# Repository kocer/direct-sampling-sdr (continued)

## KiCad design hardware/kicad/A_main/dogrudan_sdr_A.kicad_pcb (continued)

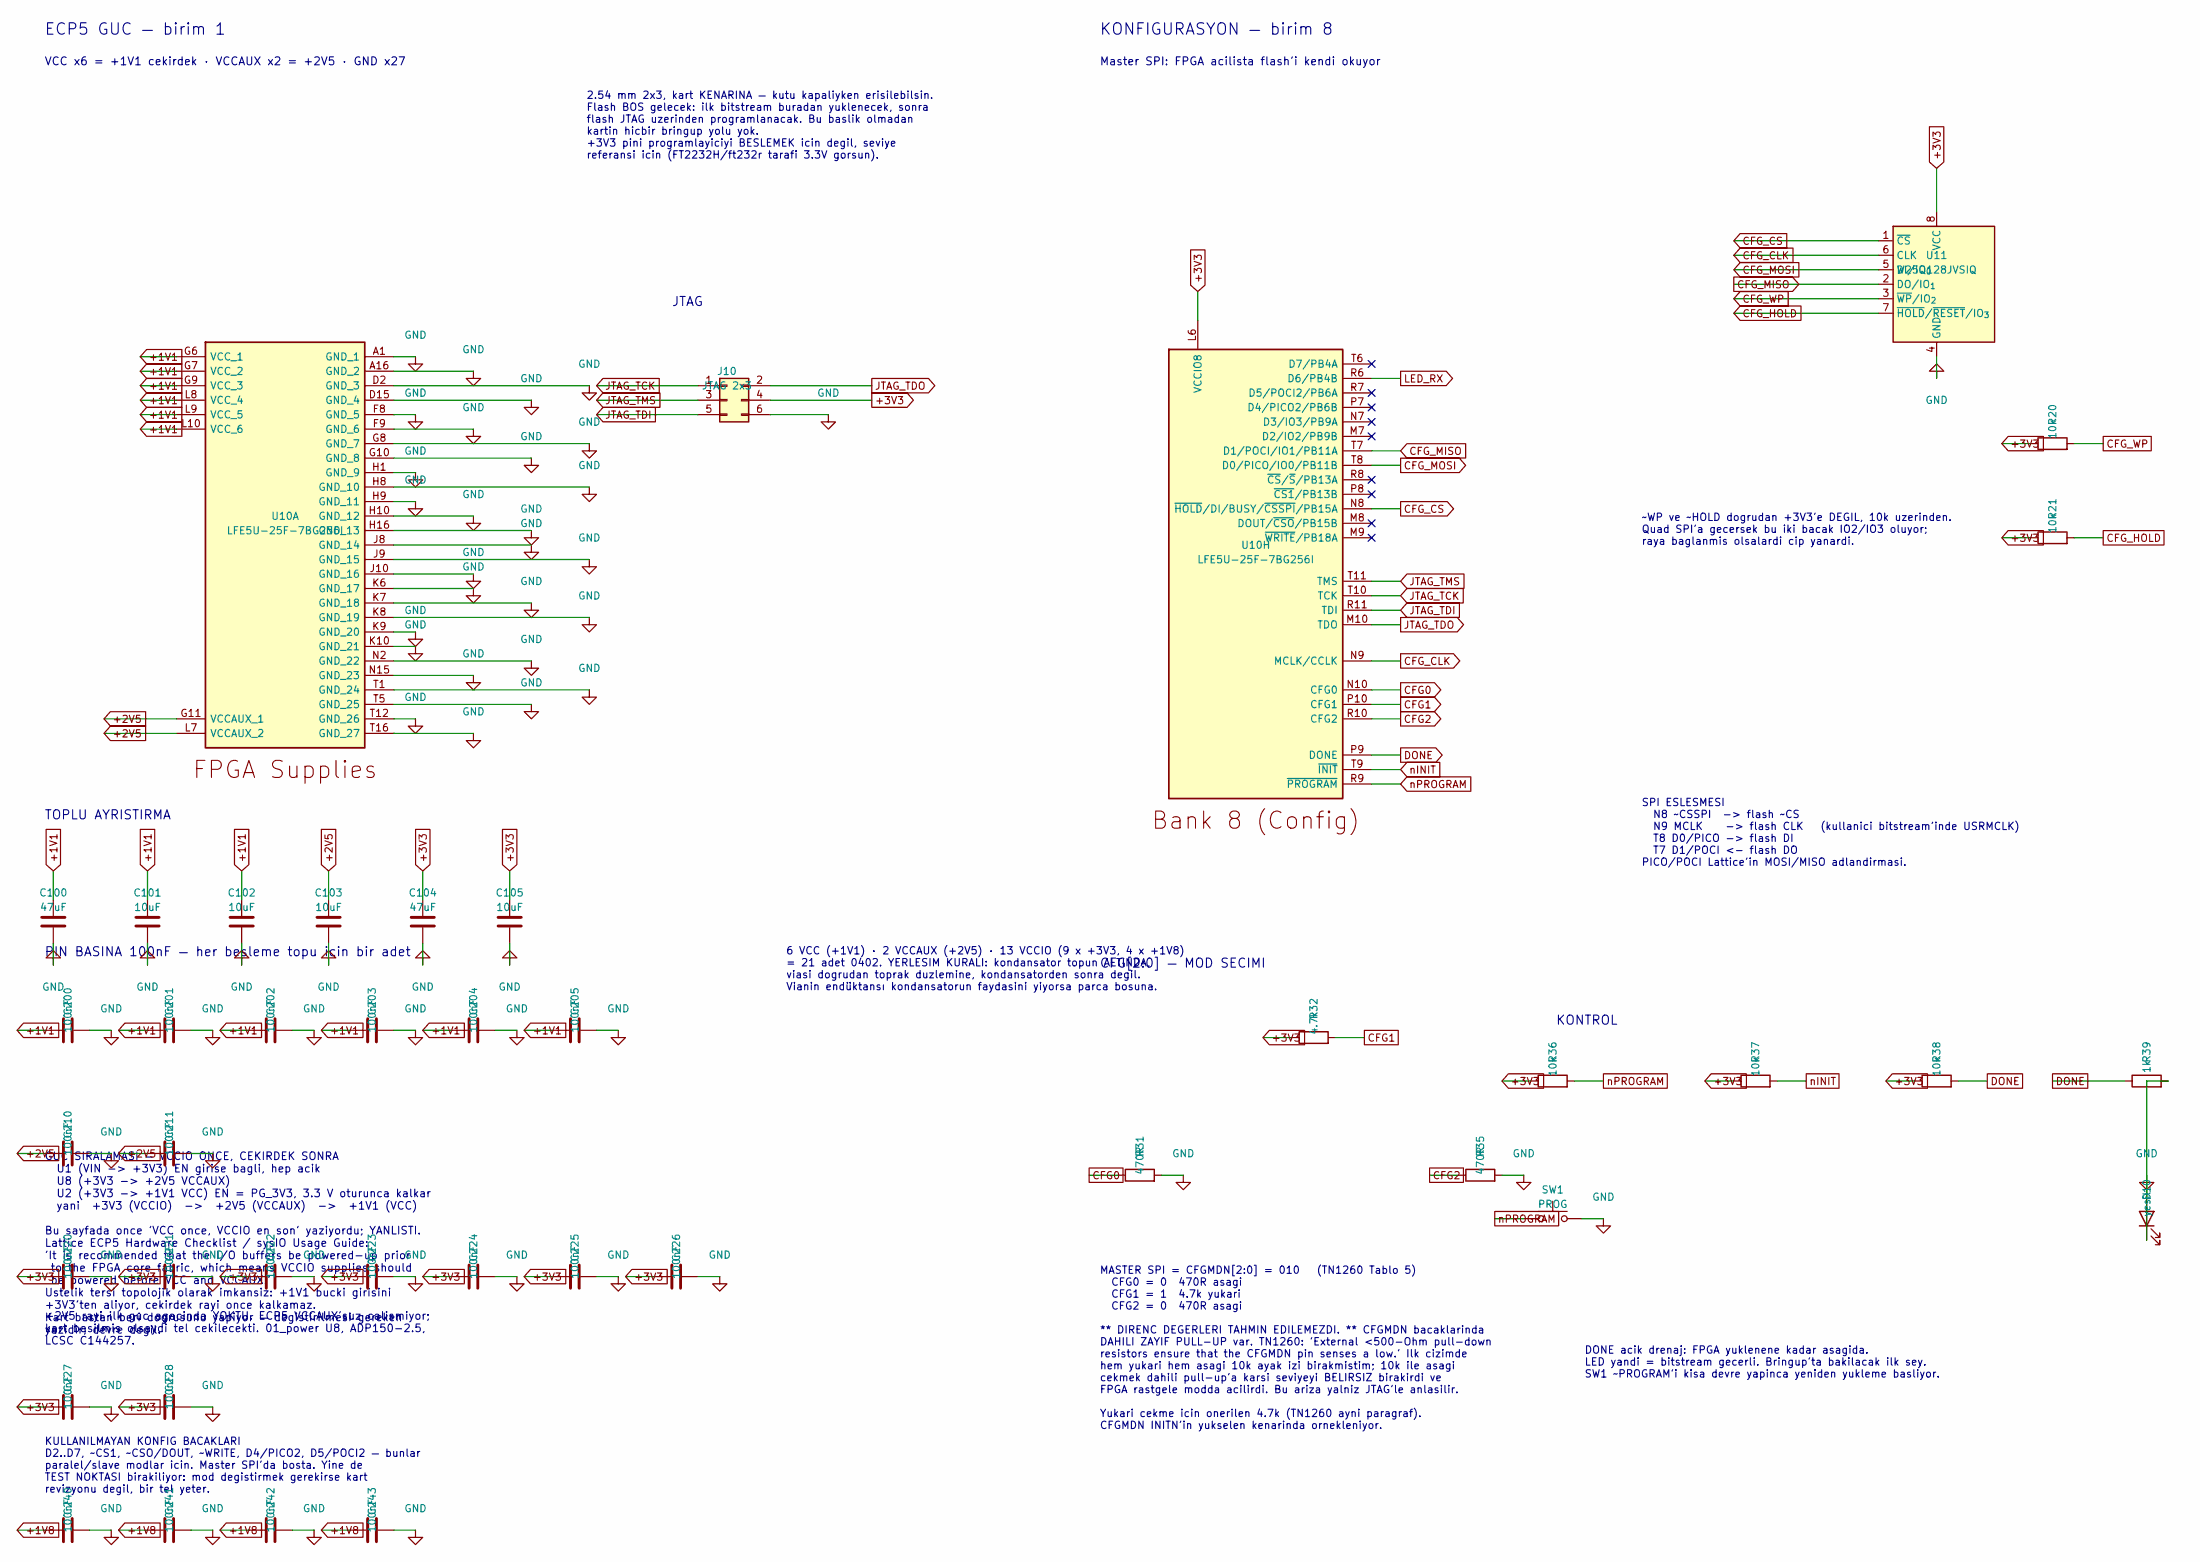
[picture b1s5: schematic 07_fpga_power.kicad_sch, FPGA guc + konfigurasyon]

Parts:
C100, C104: 47uF; C_1206_3216Metric
C101, C102, C103, C105: 10uF; C_0603_1608Metric
C200, C201, C202, C203, C204, C205, C210, C211, C220, C221, C222, C223, C224, C225, C226, C227, C228, C240, C241, C242, C243: 100nF; C_0402_1005Metric
D10: yesil; LED_0603_1608Metric
J10: JTAG 2x3; PinHeader_2x03_P2.54mm_Vertical
R20, R21, R36, R37, R38: 10k; R_0603_1608Metric
R31, R35: 470R; R_0603_1608Metric
R32: 4.7k; R_0603_1608Metric
R39: 1k; R_0603_1608Metric
SW1: PROG; SW_SPST_TL3342
U10: LFE5U-25F-7BG256I; BGA-256_14.0x14.0mm_Layout16x16_P0.8mm_Ball0.45mm_Pad0.32mm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
U11: W25Q128JVSIQ; SOIC-8_5.3x5.3mm_P1.27mm

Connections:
+1V8: C240.1, C241.1, C242.1, C243.1; also elsewhere on the board
CFG0: R31.1, U10.N10 (CFG0)
CFG1: R32.2, U10.P10 (CFG1)
CFG2: R35.1, U10.R10 (CFG2)
CFG_CLK: U10.N9 (MCLK/CCLK), U11.6 (CLK)
CFG_CS: U10.N8 (~HOLD/DI/BUSY/~CSSPI/PB15A), U11.1 (~CS)
CFG_HOLD: R21.2, U11.7 (~HOLD/~RESET/IO_{3})
CFG_MISO: U10.T7 (D1/POCI/IO1/PB11A), U11.2 (DO/IO_{1})
CFG_MOSI: U10.T8 (D0/PICO/IO0/PB11B), U11.5 (DI/IO_{0})
CFG_WP: R20.2, U11.3 (~WP/IO_{2})
DONE: R38.2, R39.1, U10.P9 (DONE); also elsewhere on the board
JTAG_TCK: J10.1, U10.T10 (TCK)
JTAG_TDI: J10.5, U10.R11 (TDI)
JTAG_TDO: J10.2, U10.M10 (TDO)
JTAG_TMS: J10.3, U10.T11 (TMS)
LED_RX: U10.R6 (D6/PB4B); also elsewhere on the board
nINIT: R37.2, U10.T9 (~INIT); also elsewhere on the board
nPROGRAM: R36.2, SW1.1, U10.R9 (~PROGRAM)

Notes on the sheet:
ECP5 GUC — birim 1
6 VCC (+1V1) · 2 VCCAUX (+2V5) · 13 VCCIO (9 x +3V3, 4 x +1V8) = 21 adet 0402. YERLESIM KURALI: kondansator topun ALTINDA, viasi dogrudan toprak duzlemine, kondansatorden sonra degil. Vianin endüktansı kondansatorun faydasini yiyorsa parca bosuna.
KULLANILMAYAN KONFIG BACAKLARI D2..D7, ~CS1, ~CSO/DOUT, ~WRITE, D4/PICO2, D5/POCI2 — bunlar paralel/slave modlar icin. Master SPI'da bosta. Yine de TEST NOKTASI birakiliyor: mod degistirmek gerekirse kart revizyonu degil, bir tel yeter.
JTAG
2.54 mm 2x3, kart KENARINA — kutu kapaliyken erisilebilsin. Flash BOS gelecek: ilk bitstream buradan yuklenecek, sonra flash JTAG uzerinden programlanacak. Bu baslik olmadan kartin hicbir bringup yolu yok. +3V3 pini programlayiciyi BESLEMEK icin degil, seviye referansi icin (FT2232H/ft232r tarafi 3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
~WP ve ~HOLD dogrudan +3V3'e DEGIL, 10k uzerinden. Quad SPI'a gecersek bu iki bacak IO2/IO3 oluyor; raya baglanmis olsalardi cip yanardi.
DONE acik drenaj: FPGA yuklenene kadar asagida. LED yandi = bitstream gecerli. Bringup'ta bakilacak ilk sey. SW1 ~PROGRAM'i kisa devre yapinca yeniden yukleme basliyor.
SPI ESLESMESI N8 ~CSSPI -> flash ~CS N9 MCLK -> flash CLK (kullanici bitstream'inde USRMCLK) T8 D0/PICO -> flash DI T7 D1/POCI <- flash DO PICO/POCI Lattice'in MOSI/MISO adlandirmasi.
GUC SIRALAMASI — VCCIO ONCE, CEKIRDEK SONRA U1 (VIN -> +3V3) EN girise bagli, hep acik U8 (+3V3 -> +2V5 VCCAUX) U2 (+3V3 -> +1V1 VCC) EN = PG_3V3, 3.3 V oturunca kalkar yani +3V3 (VCCIO) -> +2V5 (VCCAUX) -> +1V1 (VCC) Bu sayfada once 'VCC once, VCCIO en son' yaziyordu; YANLISTI. Lattice ECP5 Hardwa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
VCC x6 = +1V1 cekirdek · VCCAUX x2 = +2V5 · GND x27
CFG[2:0] — MOD SECIMI
TOPLU AYRISTIRMA
MASTER SPI = CFGMDN[2:0] = 010 (TN1260 Tablo 5) CFG0 = 0 470R asagi CFG1 = 1 4.7k yukari CFG2 = 0 470R asagi ** DIRENC DEGERLERI TAHMIN EDILEMEZDI. ** CFGMDN bacaklarinda DAHILI ZAYIF PULL-UP var. TN1260: 'External <500-Ohm pull-down resistors ensure that the CFGMDN pin senses a low.' Ilk cizimde h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
KONFIGURASYON — birim 8
+2V5 rayi ilk guc agacinda YOKTU. ECP5 VCCAUX'suz calismiyor; kart basilmis olsaydi tel cekilecekti. 01_power U8, ADP150-2.5, LCSC C144257.
Master SPI: FPGA acilista flash'i kendi okuyor
PIN BASINA 100nF — her besleme topu icin bir adet
KONTROL

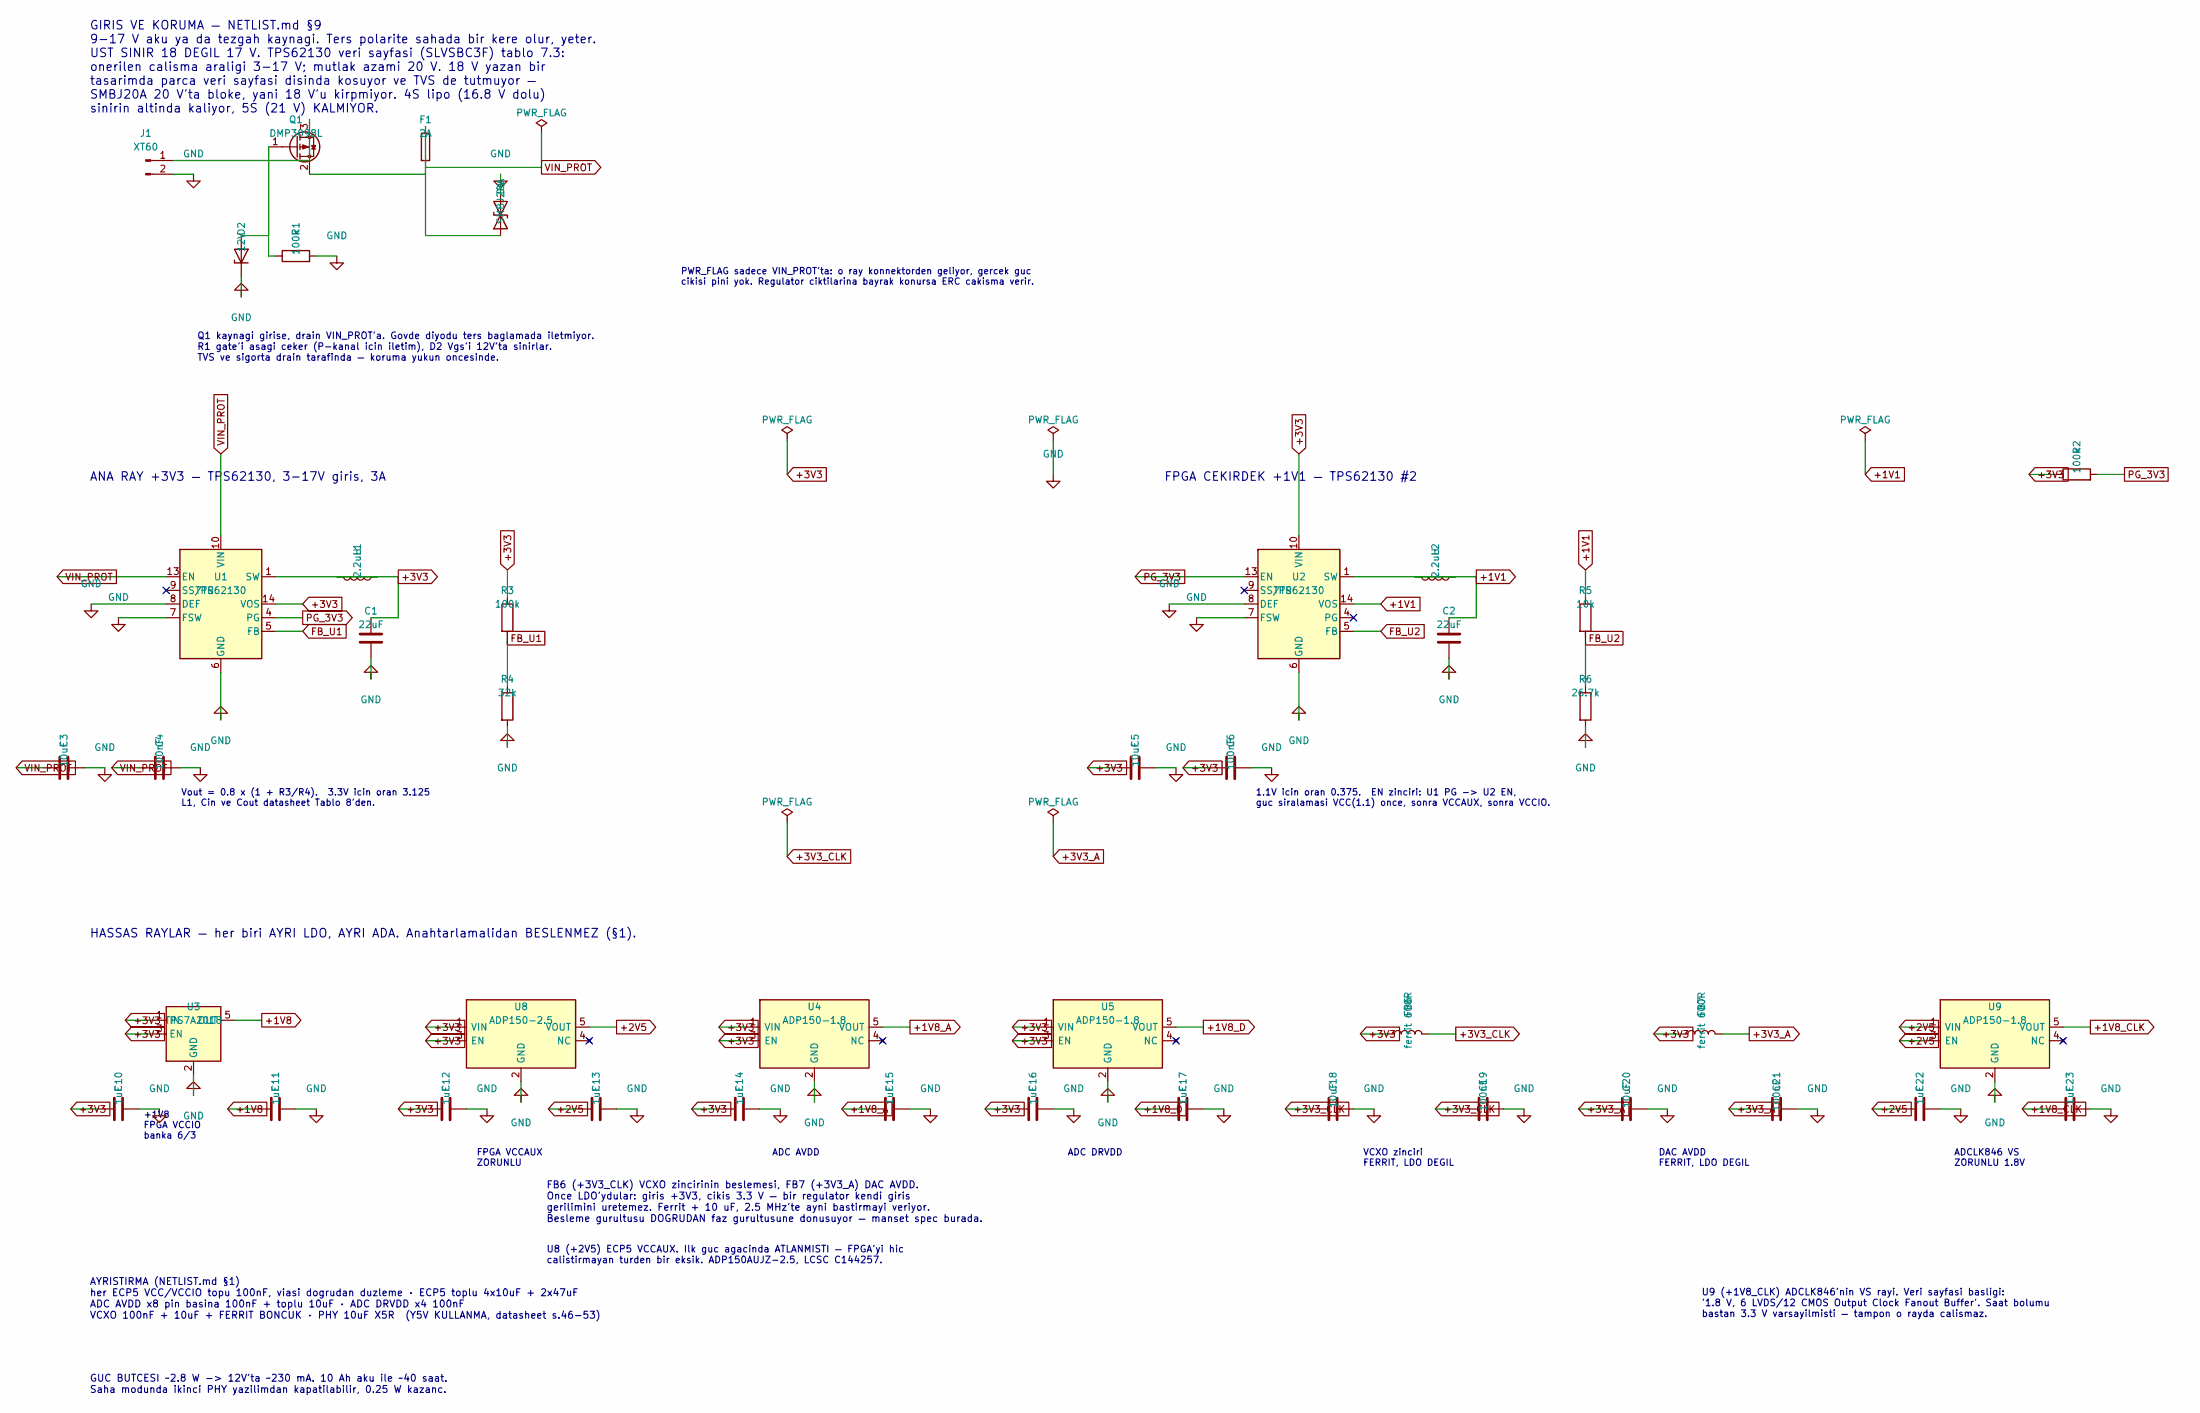
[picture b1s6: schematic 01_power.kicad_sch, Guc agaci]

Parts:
C1, C2: 22uF; C_0603_1608Metric
C3: 10uF; C_1206_3216Metric
C4, C6, C19, C21: 100nF; C_0603_1608Metric
C5: 10uF; C_0805_2012Metric
C10, C11, C12, C13, C14, C15, C16, C17, C22, C23: 1uF; C_0603_1608Metric
C18, C20: 10uF; C_0603_1608Metric
D1: SMBJ20A; D_SMB
D2: 12V; D_SOD-323
F1: 2A; Fuse_1206_3216Metric
FB6, FB7: ferrit 600R; L_0603_1608Metric
J1: XT60; SolderWire-1.5sqmm_1x02_P6mm_D1.7mm_OD3mm_Relief
L1, L2: 2.2uH; L_Taiyo-Yuden_NR-30xx
Q1: DMP3098L; SOT-23
R1, R2, R3: 100k; R_0603_1608Metric
R4: 32k; R_0603_1608Metric
R5: 10k; R_0603_1608Metric
R6: 26.7k; R_0603_1608Metric
U1, U2: TPS62130; VQFN-16-1EP_3x3mm_P0.5mm_EP1.68x1.68mm
U3: TPS7A2018; SOT-23-5
U4, U5, U9: ADP150-1.8; TSOT-23-5
U8: ADP150-2.5; TSOT-23-5

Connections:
+1V8: C11.1, U3.5 (OUT); also elsewhere on the board
+1V8_D: C17.1, U5.5 (VOUT); also elsewhere on the board
FB_U1: R3.2, R4.1, U1.5 (FB)
FB_U2: R5.2, R6.1, U2.5 (FB)
unnamed: D2.2 (A), Q1.1 (G), R1.1
unnamed: J1.1, Q1.3 (D)
unnamed: L1.1, U1.1 (SW), U1.2 (SW), U1.3 (SW)
unnamed: L2.1, U2.1 (SW), U2.2 (SW), U2.3 (SW)
unnamed: F1.1, Q1.2 (S)
PG_3V3: R2.2, U1.4 (PG), U2.13 (EN)

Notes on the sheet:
ADC AVDD
GUC BUTCESI ~2.8 W -> 12V'ta ~230 mA. 10 Ah aku ile ~40 saat. Saha modunda ikinci PHY yazilimdan kapatilabilir, 0.25 W kazanc.
U9 (+1V8_CLK) ADCLK846'nin VS rayi. Veri sayfasi basligi: '1.8 V, 6 LVDS/12 CMOS Output Clock Fanout Buffer'. Saat bolumu bastan 3.3 V varsayilmisti — tampon o rayda calismaz.
Vout = 0.8 x (1 + R3/R4). 3.3V icin oran 3.125 L1, Cin ve Cout datasheet Tablo 8'den.
1.1V icin oran 0.375. EN zinciri: U1 PG -> U2 EN, guc siralamasi VCC(1.1) once, sonra VCCAUX, sonra VCCIO.
+1V8 FPGA VCCIO banka 6/3
DAC AVDD FERRIT, LDO DEGIL
FB6 (+3V3_CLK) VCXO zincirinin beslemesi, FB7 (+3V3_A) DAC AVDD. Once LDO'ydular: giris +3V3, cikis 3.3 V — bir regulator kendi giris gerilimini uretemez. Ferrit + 10 uF, 2.5 MHz'te ayni bastirmayi veriyor. Besleme gurultusu DOGRUDAN faz gurultusune donusuyor — manset spec burada.
PWR_FLAG sadece VIN_PROT'ta: o ray konnektorden geliyor, gercek guc cikisi pini yok. Regulator ciktilarina bayrak konursa ERC cakisma verir.
ANA RAY +3V3 — TPS62130, 3-17V giris, 3A
FPGA CEKIRDEK +1V1 — TPS62130 #2
ADC DRVDD
AYRISTIRMA (NETLIST.md §1) her ECP5 VCC/VCCIO topu 100nF, viasi dogrudan duzleme · ECP5 toplu 4x10uF + 2x47uF ADC AVDD x8 pin basina 100nF + toplu 10uF · ADC DRVDD x4 100nF VCXO 100nF + 10uF + FERRIT BONCUK · PHY 10uF X5R (Y5V KULLANMA, datasheet s.46-53)
GIRIS VE KORUMA — NETLIST.md §9 9-17 V aku ya da tezgah kaynagi. Ters polarite sahada bir kere olur, yeter. UST SINIR 18 DEGIL 17 V. TPS62130 veri sayfasi (SLVSBC3F) tablo 7.3: onerilen calisma araligi 3-17 V; mutlak azami 20 V. 18 V yazan bir tasarimda parca veri sayfasi disinda kosuyor ve TVS de 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
FPGA VCCAUX ZORUNLU
VCXO zinciri FERRIT, LDO DEGIL
Q1 kaynagi girise, drain VIN_PROT'a. Govde diyodu ters baglamada iletmiyor. R1 gate'i asagi ceker (P-kanal icin iletim), D2 Vgs'i 12V'ta sinirlar. TVS ve sigorta drain tarafinda — koruma yukun oncesinde.
ADCLK846 VS ZORUNLU 1.8V
U8 (+2V5) ECP5 VCCAUX. Ilk guc agacinda ATLANMISTI — FPGA'yi hic calistirmayan turden bir eksik. ADP150AUJZ-2.5, LCSC C144257.
HASSAS RAYLAR — her biri AYRI LDO, AYRI ADA. Anahtarlamalidan BESLENMEZ (§1).

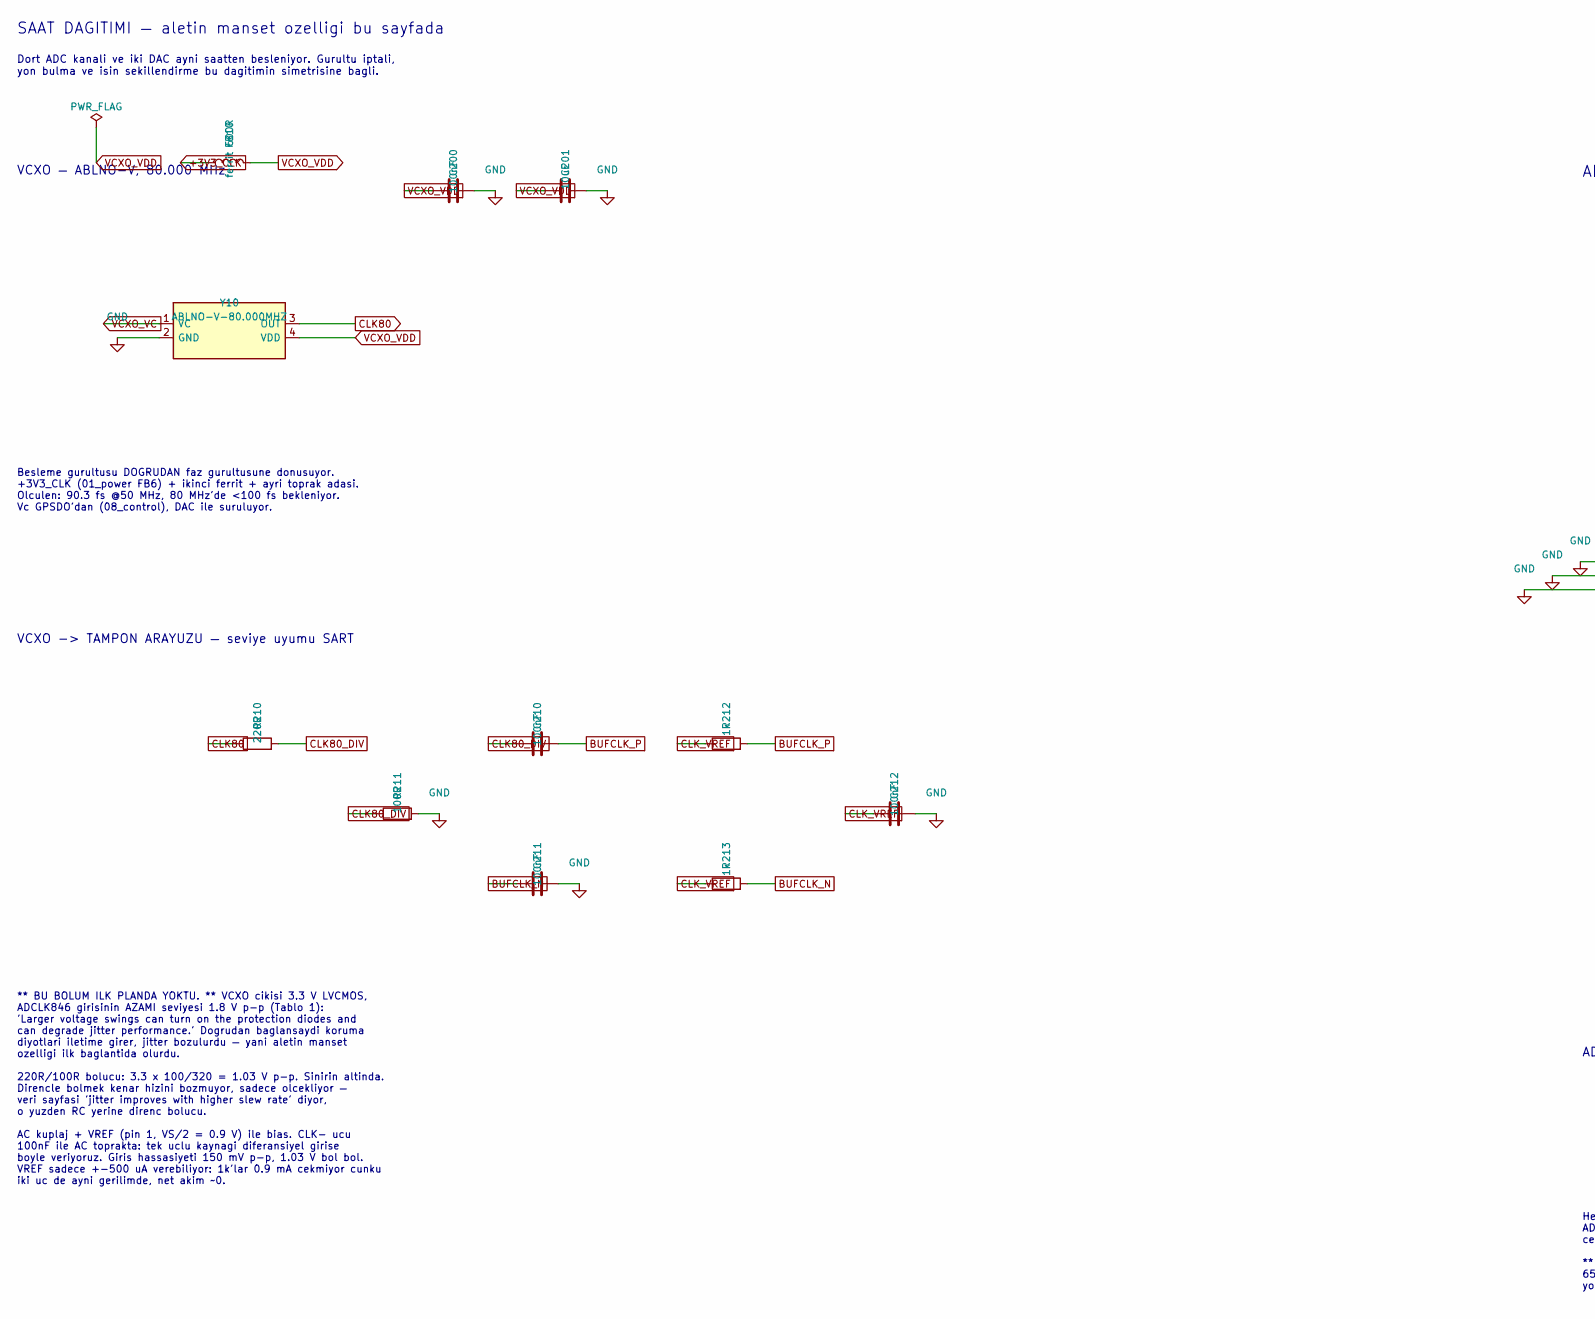
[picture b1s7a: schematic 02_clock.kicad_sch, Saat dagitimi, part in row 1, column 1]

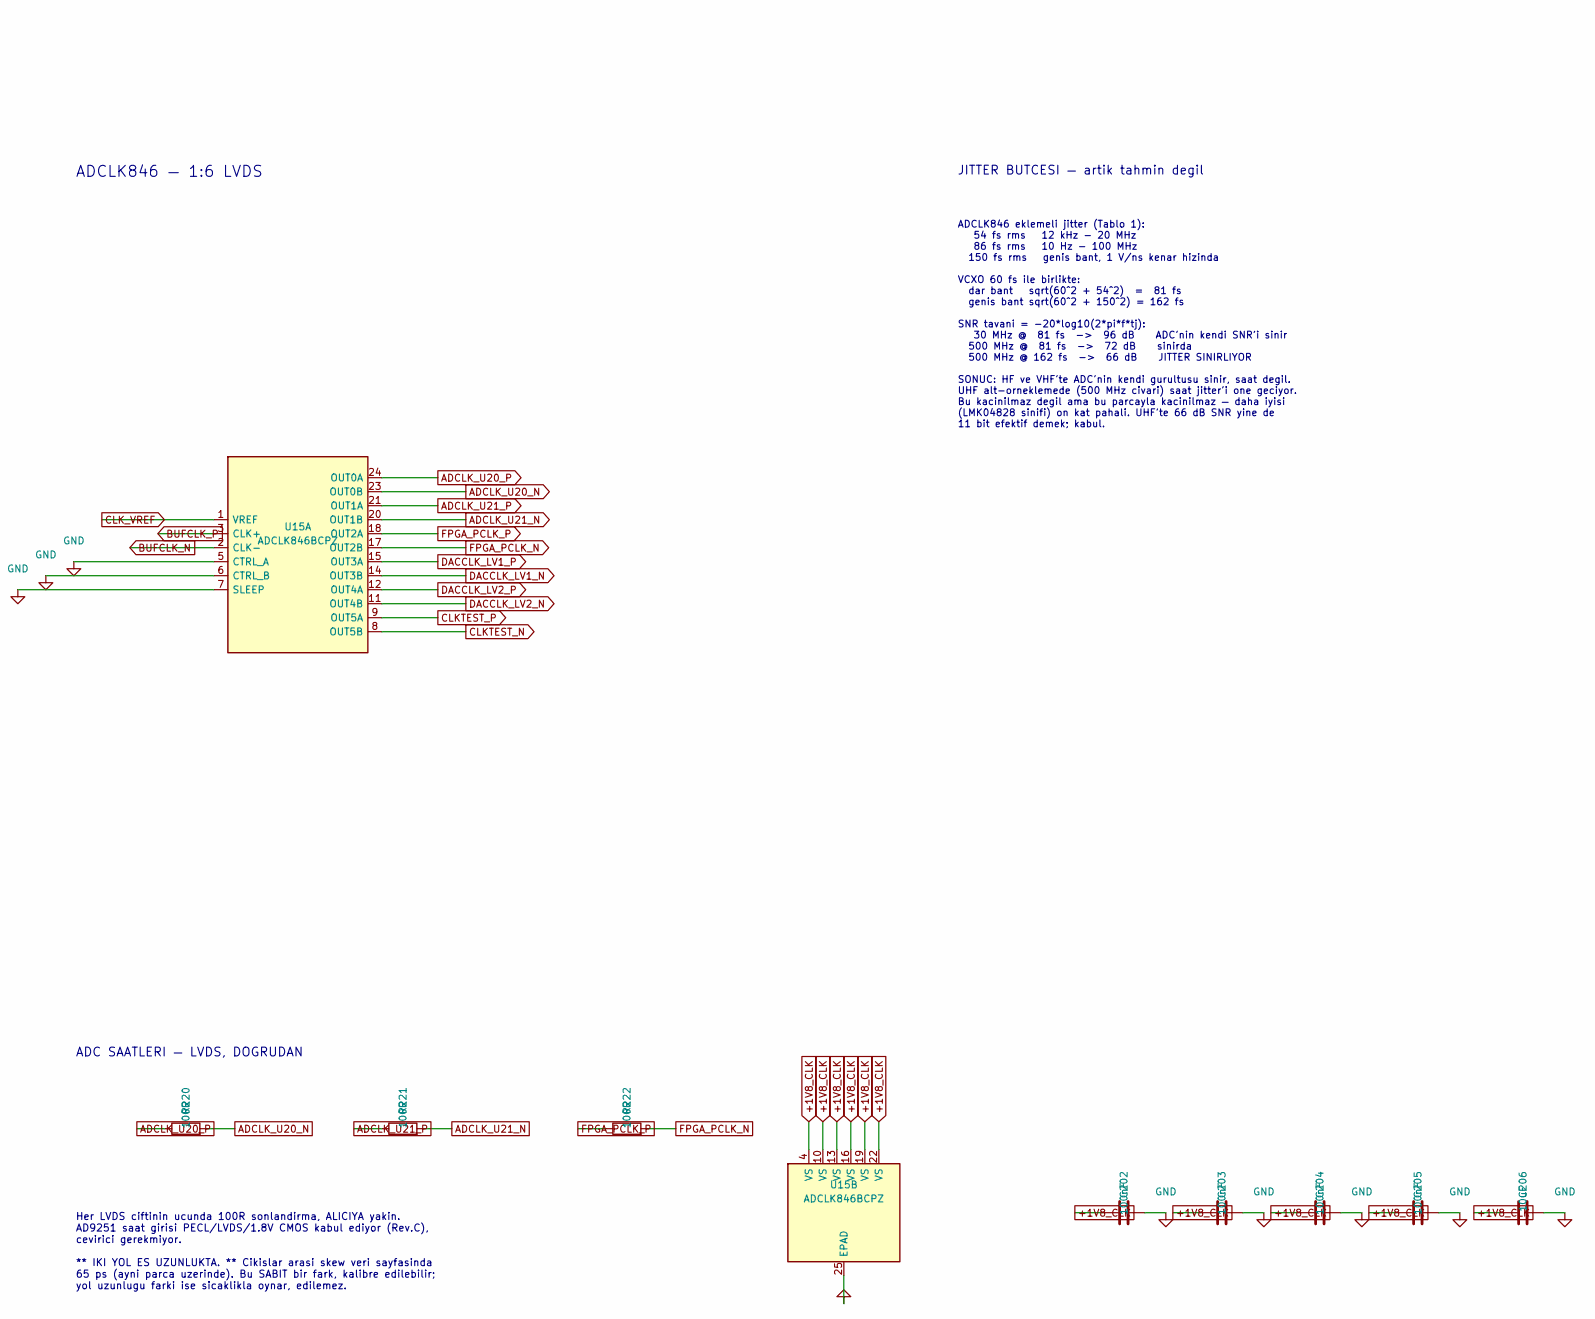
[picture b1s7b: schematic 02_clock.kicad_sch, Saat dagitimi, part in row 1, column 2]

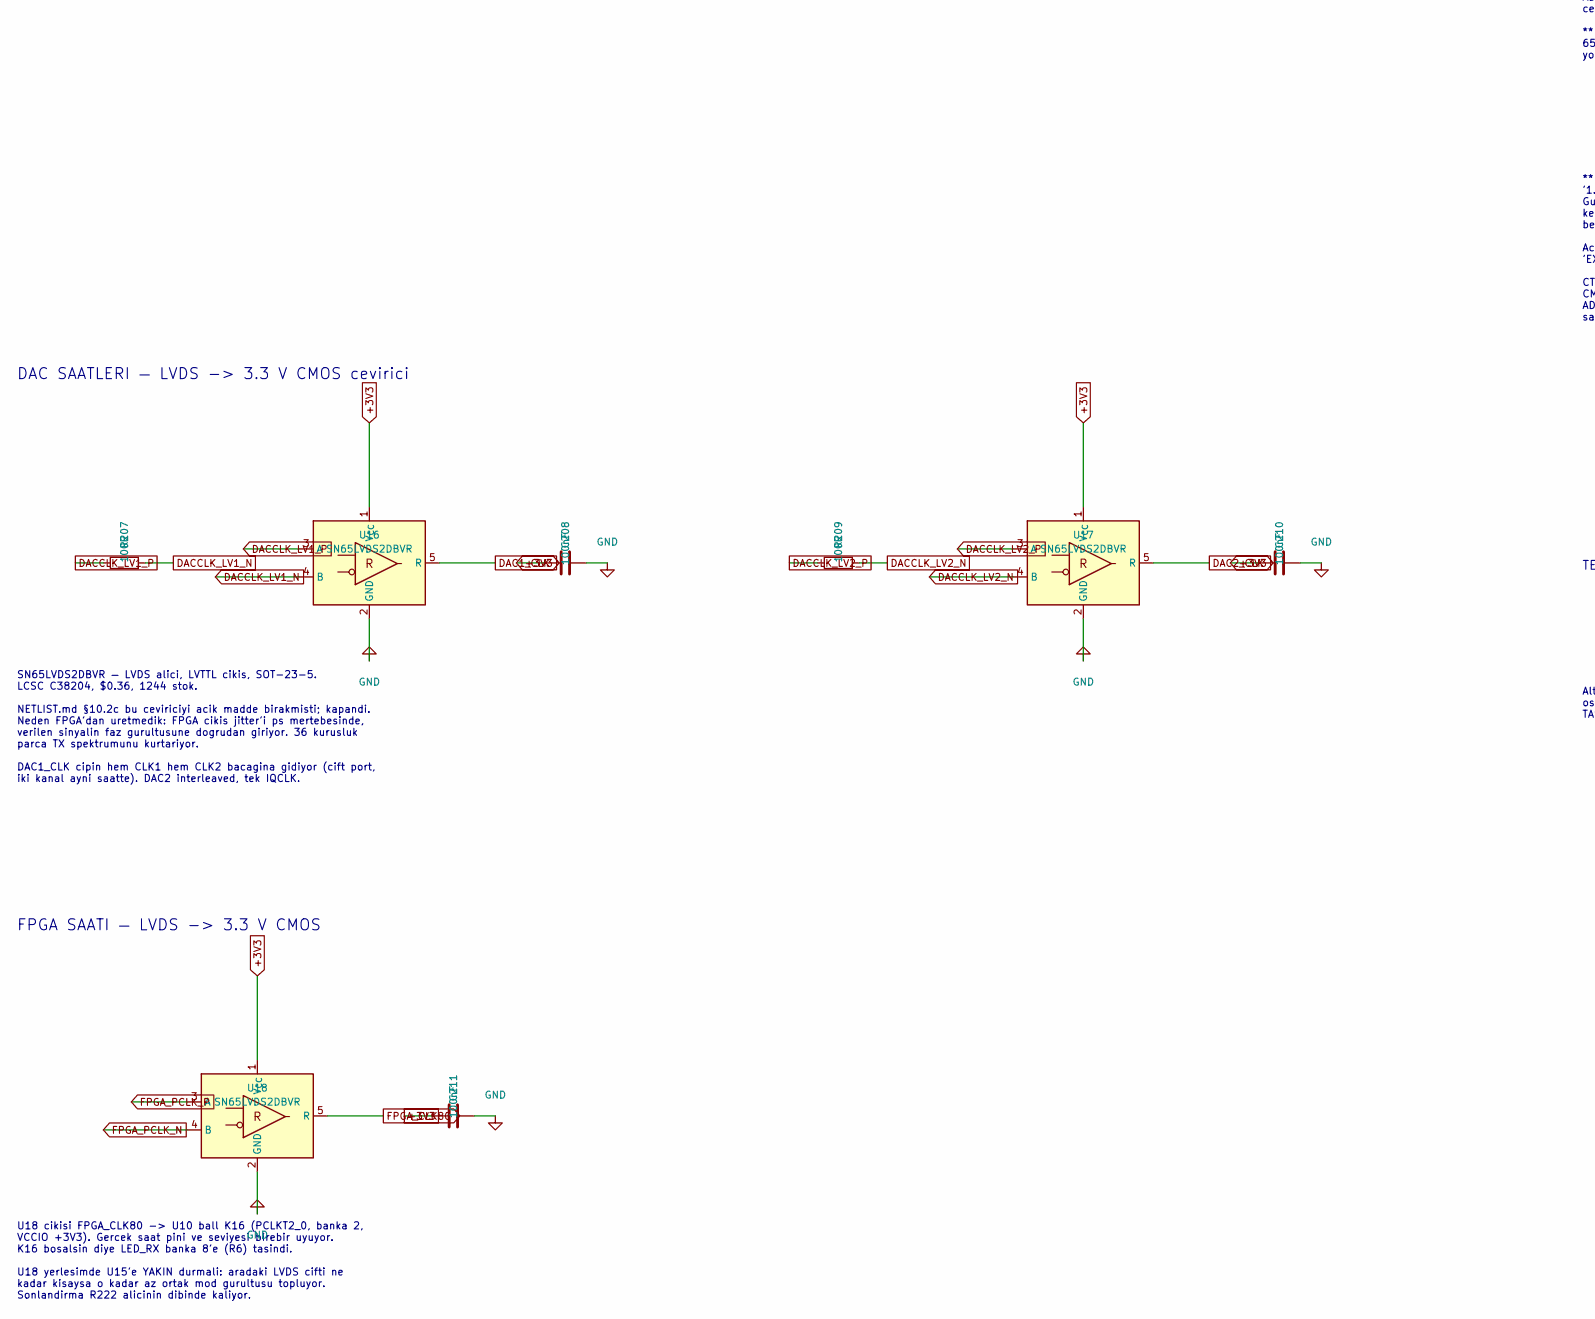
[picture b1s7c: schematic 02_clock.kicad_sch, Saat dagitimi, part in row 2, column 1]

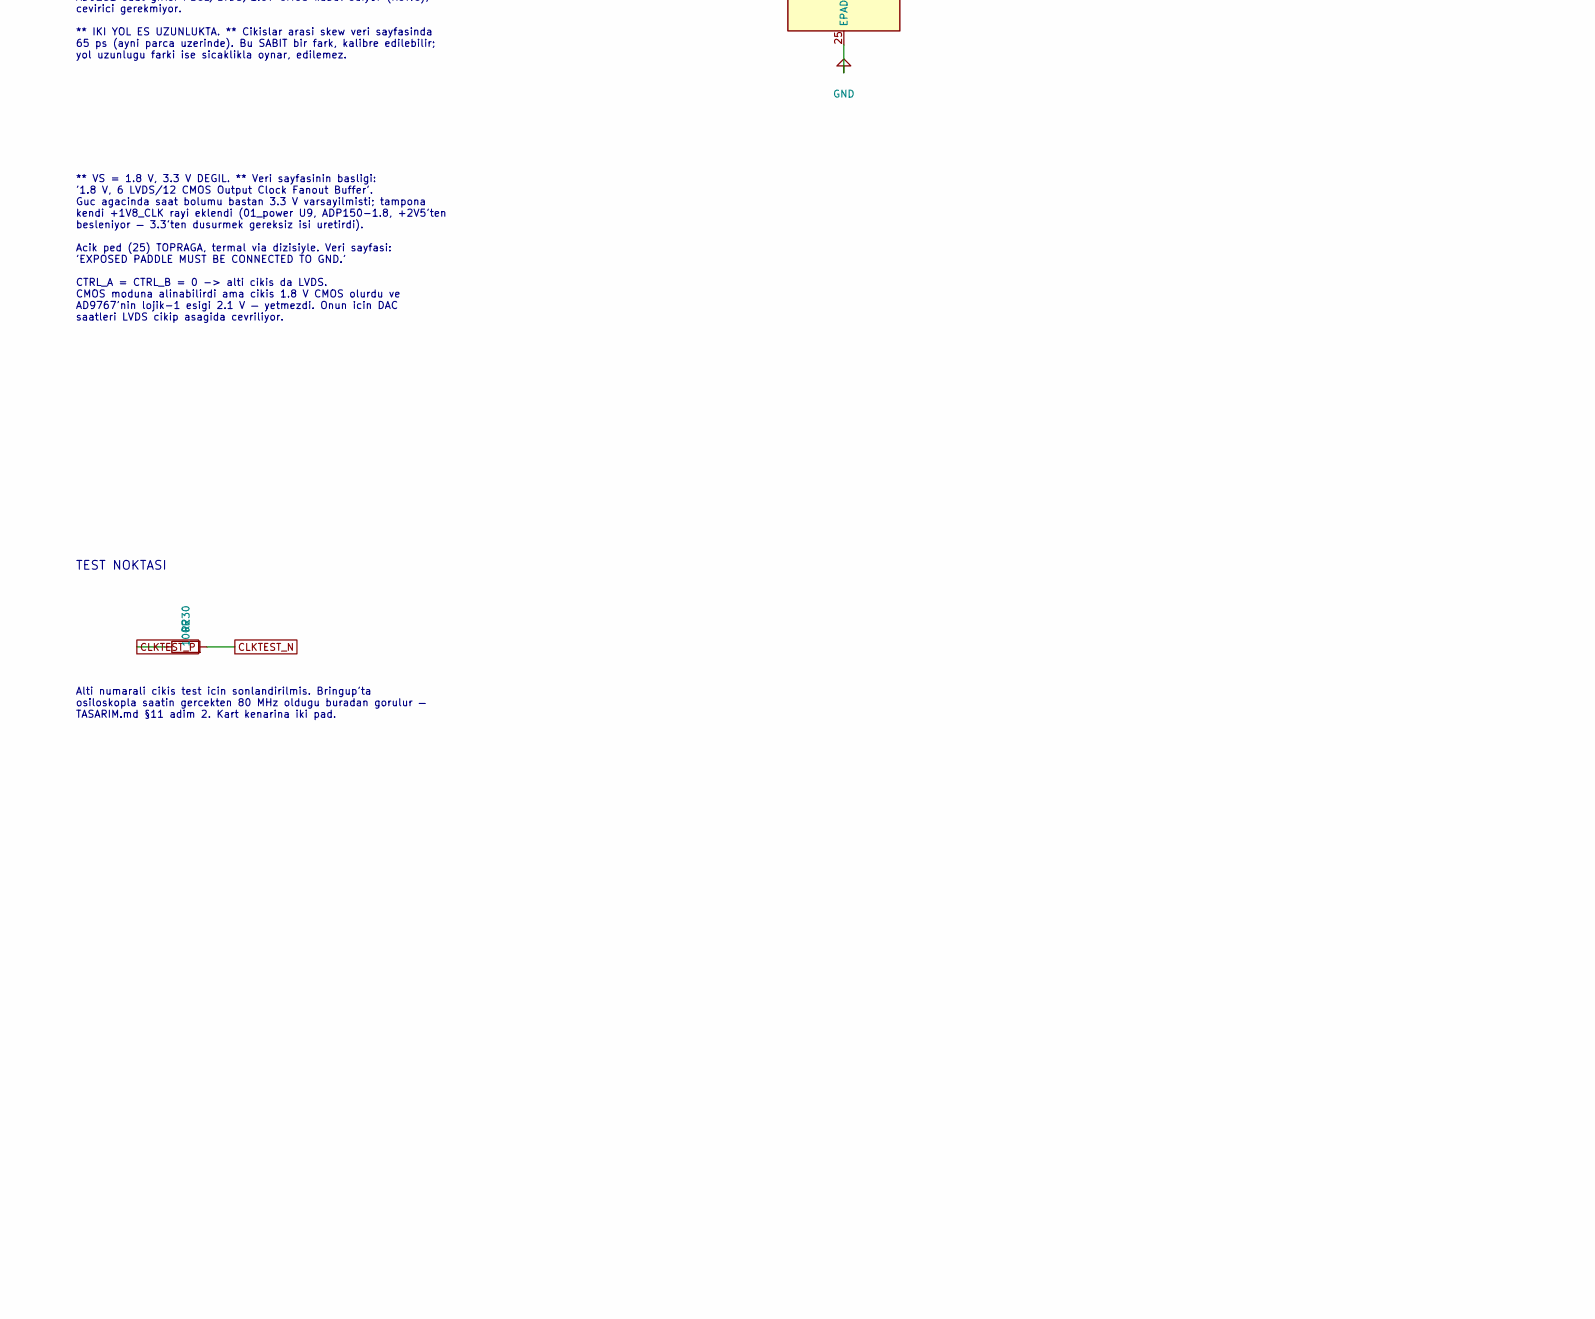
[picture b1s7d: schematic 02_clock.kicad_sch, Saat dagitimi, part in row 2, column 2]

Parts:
C200, C202, C203, C204, C205, C208, C210, C211, C212: 100nF; C_0603_1608Metric
C201, C206: 10uF; C_0603_1608Metric
FB10: ferrit 600R; L_0603_1608Metric
R207, R209, R211, R220, R221, R222, R230: 100R; R_0603_1608Metric
R210: 220R; R_0603_1608Metric
R212, R213: 1k; R_0603_1608Metric
U15: ADCLK846BCPZ; HVQFN-24-1EP_4x4mm_P0.5mm_EP2.5x2.5mm
U16, U17, U18: SN65LVDS2DBVR; SOT-23-5
Y10: ABLNO-V-80.000MHZ; Oscillator_Abracon_ABLNO_4pad_14.3x8.7mm

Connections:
ADCLK_U20_N: R220.2, U15.23 (OUT0B); also elsewhere on the board
ADCLK_U20_P: R220.1, U15.24 (OUT0A); also elsewhere on the board
ADCLK_U21_N: R221.2, U15.20 (OUT1B); also elsewhere on the board
ADCLK_U21_P: R221.1, U15.21 (OUT1A); also elsewhere on the board
CLK80: R210.1, Y10.3 (OUT)
CLKTEST_N: R230.2, U15.8 (OUT5B)
CLKTEST_P: R230.1, U15.9 (OUT5A)
CLK_VREF: C212.1, R212.1, R213.1, U15.1 (VREF)
DAC1_CLK: U16.5 (R); also elsewhere on the board
DAC2_CLK: U17.5 (R); also elsewhere on the board
DACCLK_LV1_N: R207.2, U15.14 (OUT3B), U16.4 (B)
DACCLK_LV1_P: R207.1, U15.15 (OUT3A), U16.3 (A)
DACCLK_LV2_N: R209.2, U15.11 (OUT4B), U17.4 (B)
DACCLK_LV2_P: R209.1, U15.12 (OUT4A), U17.3 (A)
FPGA_CLK80: U18.5 (R); also elsewhere on the board
FPGA_PCLK_N: R222.2, U15.17 (OUT2B), U18.4 (B)
FPGA_PCLK_P: R222.1, U15.18 (OUT2A), U18.3 (A)
VCXO_VC: Y10.1 (VC); also elsewhere on the board

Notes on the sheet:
TEST NOKTASI
FPGA SAATI — LVDS -> 3.3 V CMOS
** BU BOLUM ILK PLANDA YOKTU. ** VCXO cikisi 3.3 V LVCMOS, ADCLK846 girisinin AZAMI seviyesi 1.8 V p-p (Tablo 1): 'Larger voltage swings can turn on the protection diodes and can degrade jitter performance.' Dogrudan baglansaydi koruma diyotlari iletime girer, jitter bozulurdu — yani aletin manset 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
ADCLK846 eklemeli jitter (Tablo 1): 54 fs rms 12 kHz - 20 MHz 86 fs rms 10 Hz - 100 MHz 150 fs rms genis bant, 1 V/ns kenar hizinda VCXO 60 fs ile birlikte: dar bant sqrt(60^2 + 54^2) = 81 fs genis bant sqrt(60^2 + 150^2) = 162 fs SNR tavani = -20*log10(2*pi*f*tj): 30 MHz @ 81 fs -> 96 dB ADC'nin k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
DAC SAATLERI — LVDS -> 3.3 V CMOS cevirici
Alti numarali cikis test icin sonlandirilmis. Bringup'ta osiloskopla saatin gercekten 80 MHz oldugu buradan gorulur — TASARIM.md §11 adim 2. Kart kenarina iki pad.
SAAT DAGITIMI — aletin manset ozelligi bu sayfada
Dort ADC kanali ve iki DAC ayni saatten besleniyor. Gurultu iptali, yon bulma ve isin sekillendirme bu dagitimin simetrisine bagli.
ADCLK846 — 1:6 LVDS
Her LVDS ciftinin ucunda 100R sonlandirma, ALICIYA yakin. AD9251 saat girisi PECL/LVDS/1.8V CMOS kabul ediyor (Rev.C), cevirici gerekmiyor. ** IKI YOL ES UZUNLUKTA. ** Cikislar arasi skew veri sayfasinda 65 ps (ayni parca uzerinde). Bu SABIT bir fark, kalibre edilebilir; yol uzunlugu farki ise sica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
Besleme gurultusu DOGRUDAN faz gurultusune donusuyor. +3V3_CLK (01_power FB6) + ikinci ferrit + ayri toprak adasi. Olculen: 90.3 fs @50 MHz, 80 MHz'de <100 fs bekleniyor. Vc GPSDO'dan (08_control), DAC ile suruluyor.
U18 cikisi FPGA_CLK80 -> U10 ball K16 (PCLKT2_0, banka 2, VCCIO +3V3). Gercek saat pini ve seviyesi birebir uyuyor. K16 bosalsin diye LED_RX banka 8'e (R6) tasindi. U18 yerlesimde U15'e YAKIN durmali: aradaki LVDS cifti ne kadar kisaysa o kadar az ortak mod gurultusu topluyor. Sonlandirma R222 alic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
SN65LVDS2DBVR — LVDS alici, LVTTL cikis, SOT-23-5. LCSC C38204, $0.36, 1244 stok. NETLIST.md §10.2c bu ceviriciyi acik madde birakmisti; kapandi. Neden FPGA'dan uretmedik: FPGA cikis jitter'i ps mertebesinde, verilen sinyalin faz gurultusune dogrudan giriyor. 36 kurusluk parca TX spektrumunu kurtar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
** VS = 1.8 V, 3.3 V DEGIL. ** Veri sayfasinin basligi: '1.8 V, 6 LVDS/12 CMOS Output Clock Fanout Buffer'. Guc agacinda saat bolumu bastan 3.3 V varsayilmisti; tampona kendi +1V8_CLK rayi eklendi (01_power U9, ADP150-1.8, +2V5'ten besleniyor — 3.3'ten dusurmek gereksiz isi uretirdi). Acik ped (25)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
JITTER BUTCESI — artik tahmin degil
VCXO — ABLNO-V, 80.000 MHz
ADC SAATLERI — LVDS, DOGRUDAN
VCXO -> TAMPON ARAYUZU — seviye uyumu SART
